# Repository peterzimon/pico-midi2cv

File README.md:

# MIDI to CV converter

## About
A simple MIDI to CV converter using MCP4288 DAC.

## Dependecies
Uses [`pico-lib`](https://github.com/peterzimon/pico-lib) submodule. Clone and pull 
with `--recurse-submodules`, or use `git submodule update --init` once cloned. 

Alternatively you can set `git config submodule.recurse true` or `git config --global submodule.recurse true`.

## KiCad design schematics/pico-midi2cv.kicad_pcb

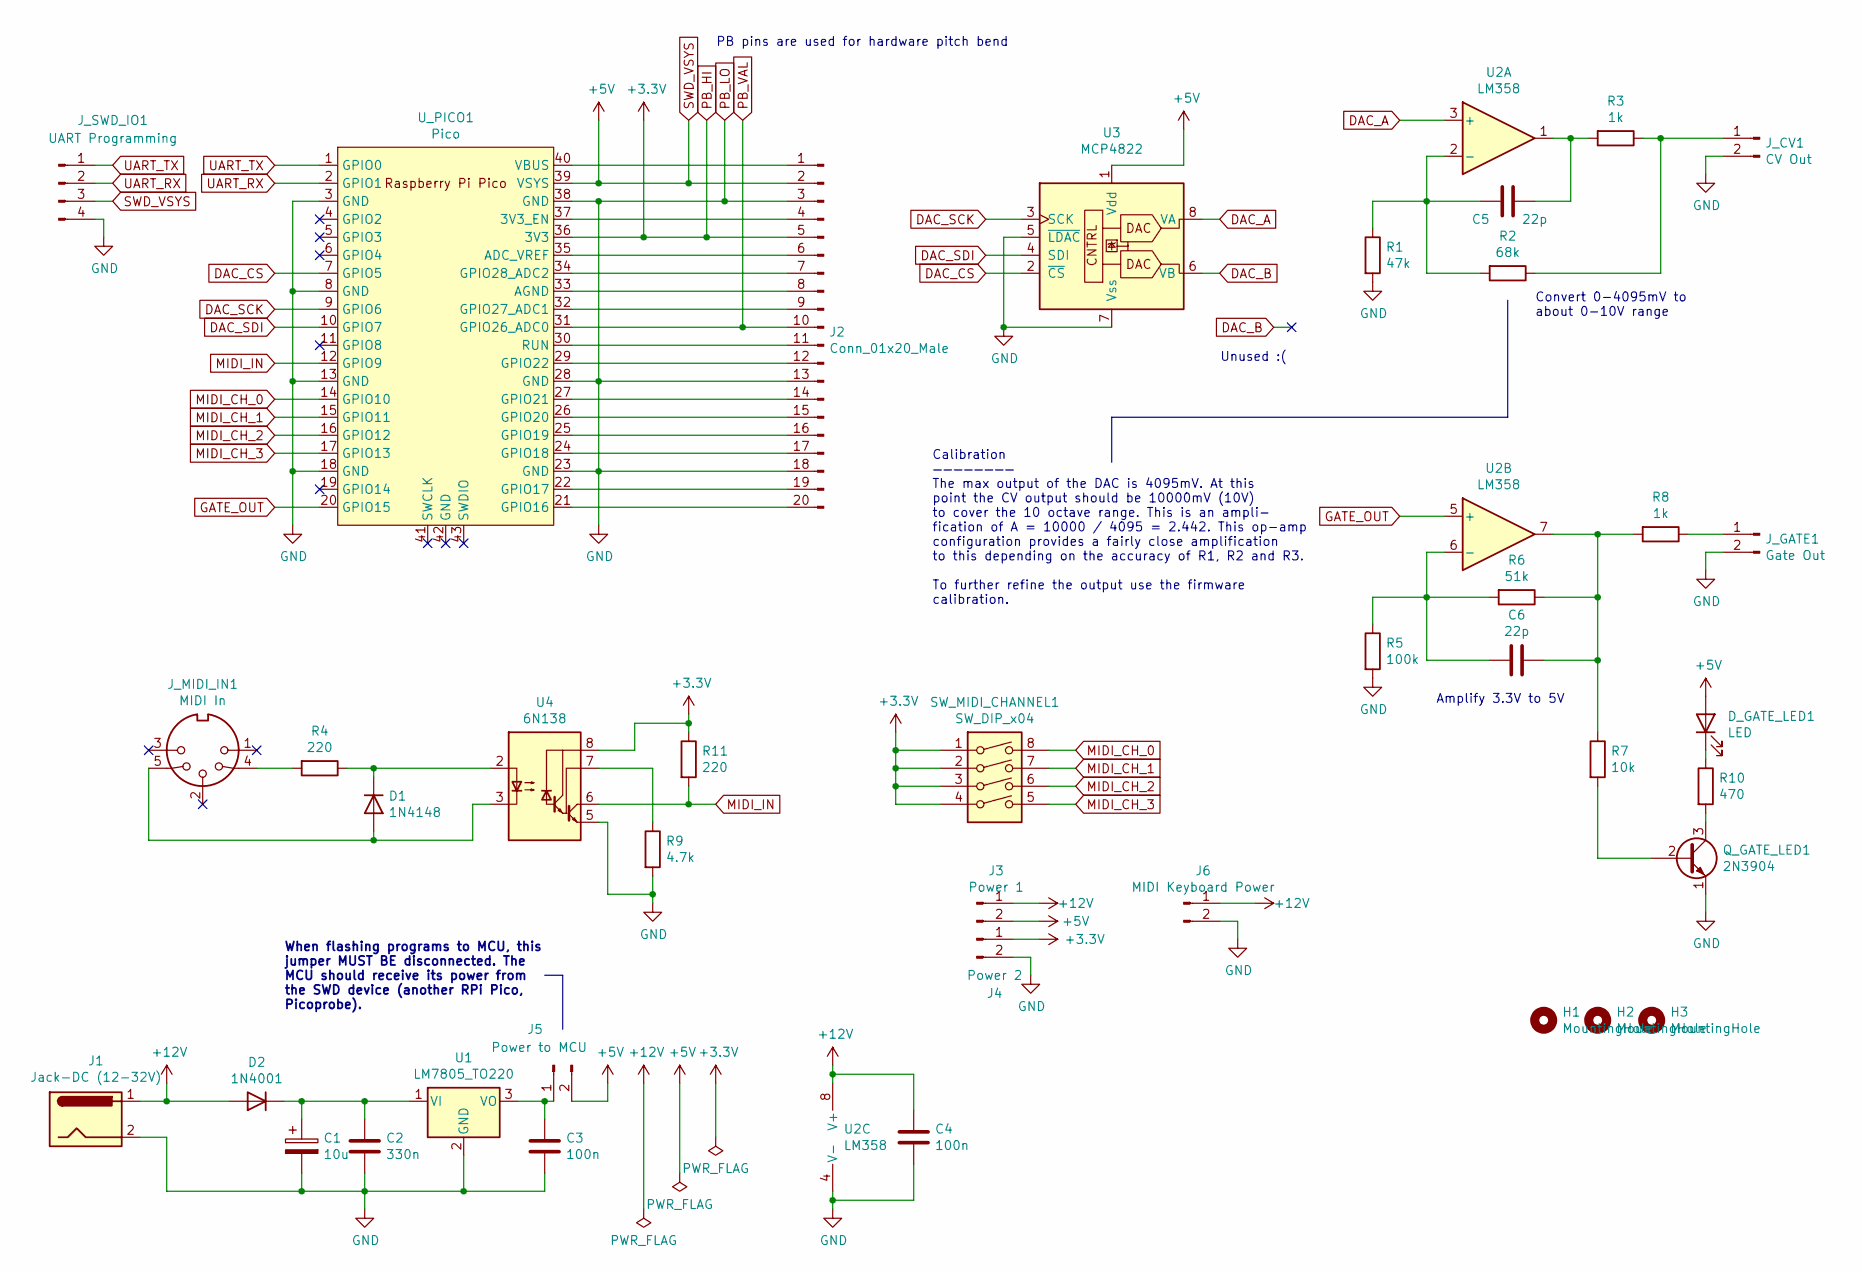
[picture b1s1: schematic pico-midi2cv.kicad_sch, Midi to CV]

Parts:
C1: 10u; CP_Radial_D5.0mm_P2.50mm
C2: 330n; C_Disc_D5.0mm_W2.5mm_P2.50mm
C3, C4: 100n; C_Disc_D5.0mm_W2.5mm_P2.50mm
C5, C6: 22p; C_Disc_D5.0mm_W2.5mm_P2.50mm
D1: 1N4148; D_Axial
D2: 1N4001; D_Axial
D_GATE_LED1: LED; NSL25_01x02_Vertical
H1, H2, H3: MountingHole; MountingHole_3mm
J1: Jack-DC (12-32V); NSL25_01x02_Vertical
J2: Conn_01x20_Male; PinOut_01x20
J3: Power 1; NSL25_01x02_Vertical
J4: Power 2; NSL25_01x02_Vertical
J5: Power to MCU; PinOut_01x02
J6: MIDI Keyboard Power; NSL25_01x02_Vertical
J_CV1: CV Out; NSL25_01x02_Vertical
J_GATE1: Gate Out; NSL25_01x02_Vertical
J_MIDI_IN1: MIDI In; PinOut_01x05
J_SWD_IO1: UART Programming; PinOut_01x04
Q_GATE_LED1: 2N3904; TO-92_Inline_Wide
R1: 47k; R_Axial_Vertical
R2: 68k; R_Axial_Vertical
R3, R8: 1k; R_Axial_Vertical
R4, R11: 220; R_Axial_Vertical
R5: 100k; R_Axial_Vertical
R6: 51k; R_Axial_Vertical
R7: 10k; R_Axial_Vertical
R9: 4.7k; R_Axial_Vertical
R10: 470; R_Axial_Vertical
SW_MIDI_CHANNEL1: SW_DIP_x04; SW_DIP_SPSTx04_Slide_6.7x11.72mm_W7.62mm_P2.54mm_LowProfile
U1: LM7805_TO220; TO-220-3_Vertical
U2: LM358; DIP-8_W7.62mm
U3: MCP4822; DIP-8_W7.62mm
U4: 6N138; DIP-8_W7.62mm
U_PICO1: Pico; RPi_Pico_SMD_TH

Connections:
+12V: C4.1, D2.2 (A), J1.1, J3.1, J6.1, U2.8 (V+)
DAC_A: U2.3 (+), U3.8 (VA)
DAC_B: U3.6 (VB)
DAC_CS: U3.2 (~CS), U_PICO1.7 (GPIO5)
DAC_SCK: U3.3 (SCK), U_PICO1.9 (GPIO6)
DAC_SDI: U3.4 (SDI), U_PICO1.10 (GPIO7)
GATE_OUT: U2.5 (+), U_PICO1.20 (GPIO15)
MIDI_CH_0: SW_MIDI_CHANNEL1.8, U_PICO1.14 (GPIO10)
MIDI_CH_1: SW_MIDI_CHANNEL1.7, U_PICO1.15 (GPIO11)
MIDI_CH_2: SW_MIDI_CHANNEL1.6, U_PICO1.16 (GPIO12)
MIDI_CH_3: SW_MIDI_CHANNEL1.5, U_PICO1.17 (GPIO13)
MIDI_IN: R11.2, U4.6 (VO2), U_PICO1.12 (GPIO9)
unnamed: C1.1, C2.1, D2.1 (K), U1.1 (VI)
unnamed: C3.1, J5.1, U1.3 (VO)
unnamed: C5.1, R3.2, U2.1
unnamed: C5.2, R1.1, R2.2, U2.2 (-)
unnamed: C6.1, R6.1, R7.1, R8.2, U2.7
unnamed: C6.2, R5.1, R6.2, U2.6 (-)
unnamed: D1.1 (K), R4.1, U4.2 (C1)
unnamed: D1.2 (A), J_MIDI_IN1.5, U4.3 (C2)
unnamed: D_GATE_LED1.1 (K), R10.1
unnamed: J2.1, U_PICO1.40 (VBUS)
unnamed: J2.4, U_PICO1.37 (3V3_EN)
unnamed: J2.6, U_PICO1.35 (ADC_VREF)
unnamed: J2.7, U_PICO1.34 (GPIO28_ADC2)
unnamed: J2.8, U_PICO1.33 (AGND)
unnamed: J2.9, U_PICO1.32 (GPIO27_ADC1)
unnamed: J2.11, U_PICO1.30 (RUN)
unnamed: J2.12, U_PICO1.29 (GPIO22)
unnamed: J2.14, U_PICO1.27 (GPIO21)
unnamed: J2.15, U_PICO1.26 (GPIO20)
unnamed: J2.16, U_PICO1.25 (GPIO19)
unnamed: J2.17, U_PICO1.24 (GPIO18)
unnamed: J2.19, U_PICO1.22 (GPIO17)
unnamed: J2.20, U_PICO1.21 (GPIO16)
unnamed: J_CV1.1, R2.1, R3.1
unnamed: J_GATE1.1, R8.1
unnamed: J_MIDI_IN1.4, R4.2
unnamed: Q_GATE_LED1.2 (B), R7.2
unnamed: Q_GATE_LED1.3 (C), R10.2
unnamed: R9.1, U4.7 (VO1)
PB_HI: J2.5, J4.1, R11.1, SW_MIDI_CHANNEL1.1, SW_MIDI_CHANNEL1.2, SW_MIDI_CHANNEL1.3, SW_MIDI_CHANNEL1.4, U4.8 (VCC), U_PICO1.36 (3V3)
PB_LO: C1.2, C2.2, C3.2, C4.2, J1.2, J2.3, J2.13, J2.18, J4.2, J6.2, J_CV1.2, J_GATE1.2, J_SWD_IO1.4, Q_GATE_LED1.1 (E), R1.2, R5.2, R9.2, U1.2 (GND), U2.4 (V-), U3.5 (~LDAC), U3.7 (Vss), U4.5 (GND), U_PICO1.3 (GND), U_PICO1.8 (GND), U_PICO1.13 (GND), U_PICO1.18 (GND), U_PICO1.23 (GND), U_PICO1.28 (GND), U_PICO1.38 (GND)
PB_VAL: J2.10, U_PICO1.31 (GPIO26_ADC0)
SWD_VSYS: D_GATE_LED1.2 (A), J2.2, J3.2, J5.2, J_SWD_IO1.3, U3.1 (Vdd), U_PICO1.39 (VSYS)
UART_RX: J_SWD_IO1.2, U_PICO1.2 (GPIO1)
UART_TX: J_SWD_IO1.1, U_PICO1.1 (GPIO0)

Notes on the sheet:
Amplify 3.3V to 5V
PB pins are used for hardware pitch bend
Convert 0-4095mV to about 0-10V range
Unused :(
When flashing programs to MCU, this jumper MUST BE disconnected. The MCU should receive its power from the SWD device (another RPi Pico, Picoprobe).
Calibration ———————— The max output of the DAC is 4095mV. At this point the CV output should be 10000mV (10V) to cover the 10 octave range. This is an ampli- fication of A = 10000 / 4095 = 2.442. This op-amp configuration provides a fairly close amplification to this depending on the accuracy of R1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

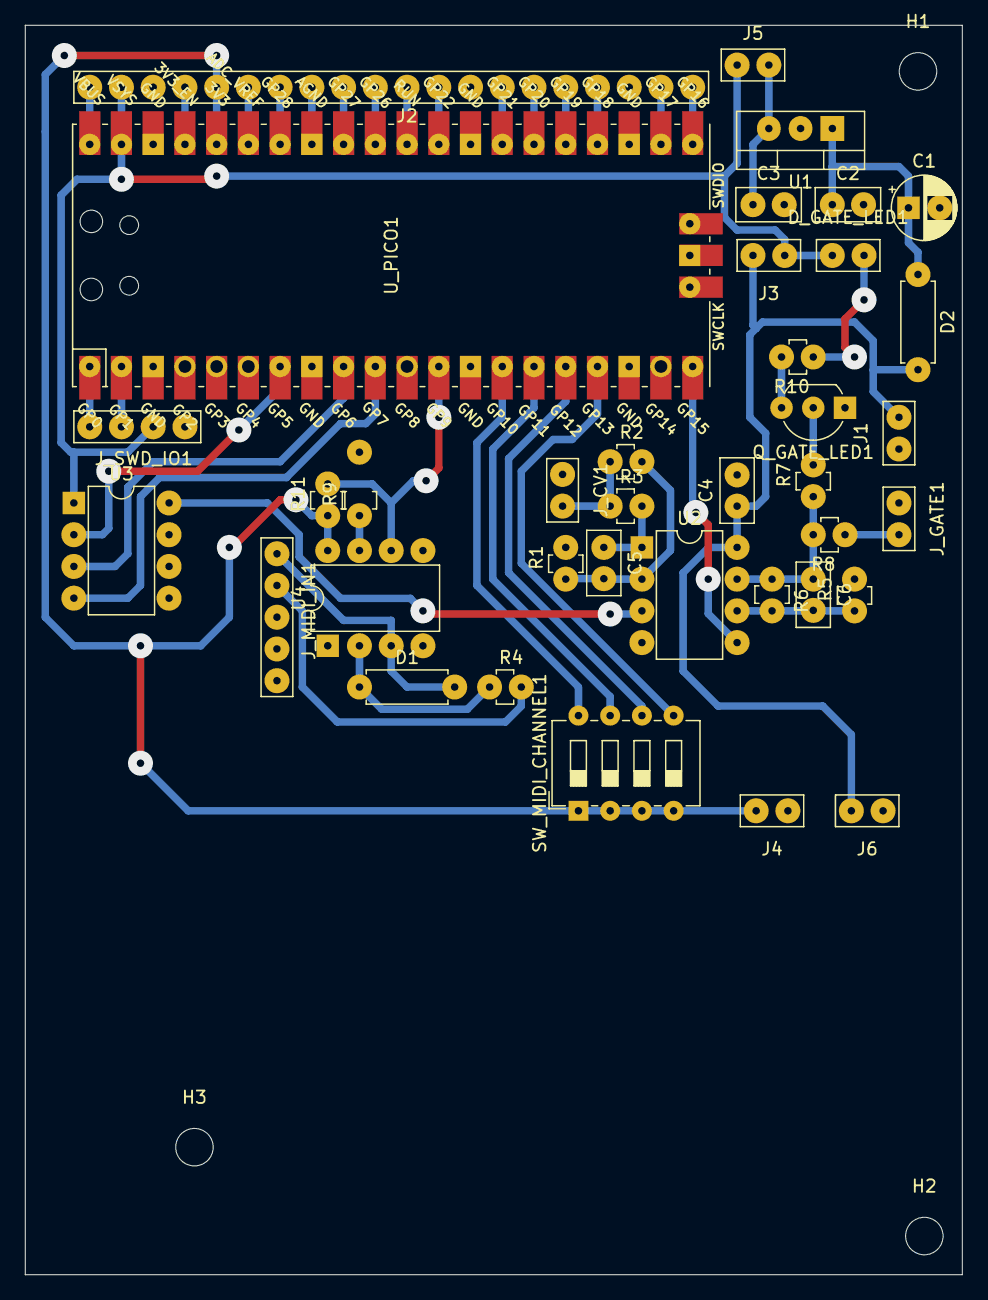
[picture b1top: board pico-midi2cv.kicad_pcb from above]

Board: 2 copper layers, 75.0 x 100.0 mm, 40 parts (0 on the bottom side), 46 nets.

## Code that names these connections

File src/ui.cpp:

#include "ui.h"

void UI::init() {
    // Read MIDI channel. Only do this once during bootup
    gpio_init(GP_CHANNEL_DIP_0); gpio_set_dir(GP_CHANNEL_DIP_0, GPIO_IN); gpio_pull_down(GP_CHANNEL_DIP_0);
    gpio_init(GP_CHANNEL_DIP_1); gpio_set_dir(GP_CHANNEL_DIP_1, GPIO_IN); gpio_pull_down(GP_CHANNEL_DIP_1);
    gpio_init(GP_CHANNEL_DIP_2); gpio_set_dir(GP_CHANNEL_DIP_2, GPIO_IN); gpio_pull_down(GP_CHANNEL_DIP_2);
    gpio_init(GP_CHANNEL_DIP_3); gpio_set_dir(GP_CHANNEL_DIP_3, GPIO_IN); gpio_pull_down(GP_CHANNEL_DIP_3);

    int midi_ch_0 = gpio_get(GP_CHANNEL_DIP_0);
    int midi_ch_1 = gpio_get(GP_CHANNEL_DIP_1);
    int midi_ch_2 = gpio_get(GP_CHANNEL_DIP_2);
    int midi_ch_3 = gpio_get(GP_CHANNEL_DIP_3);

    uint8_t midi_ch = midi_ch_0 | midi_ch_1 << 1 | midi_ch_2 << 2 | midi_ch_3;
    settings.midi_channel = midi_ch;

    printf("Midi channel: %d\r\n", midi_ch);

    // Pitchbend initialisation
    // Init ADC
    adc_init();
    adc_gpio_init(ADC_GP_PITCHBEND);

    // Select a GPIO port for input. 0 represents GPIO26, 1: GPIO27 etc. Subtract
    // 26 from the GPIO port number to get the mapping.
    adc_select_input(ADC_GP_PITCHBEND - 26);

    // Store initial value of pitchbend as a reference point
    m_pitchbend_reference = m_read_adc_samples(10);

    // printf("Pitchbend reference: %d", m_pitchbend_reference);
}

// Read all values on the UI
void UI::update() {
    m_update_pitchbend();
}

/**
 * Return the pitch bend value converted to MIDI value
 * 1. m_pitchbend_reference should be mapped to PITCH_BEND_CENTER (0x2000)
 * 2. m_pitchbend_reference +/- HW_PB_MAX_DIFF should be mapped to
 *    MAX_PITCH_BEND (0x3fff) and 0x0000 respectively
 * 3. Returned value should not be between 0 and 0x3fff
 */
uint16_t UI::hw_pb_to_midi_pb() {
    uint16_t midi_pitchbend = 0x0;
    uint16_t diff = 0;
    uint16_t ratio = 0;

    if (m_pitchbend > m_pitchbend_reference) {
        diff = m_pitchbend - m_pitchbend_reference;
        ratio = round(diff * 100 / HW_PB_MAX_DIFF);
        midi_pitchbend = uint16_t(PITCH_BEND_CENTER + (PITCH_BEND_CENTER * ratio / 100));
    } else if (m_pitchbend < m_pitchbend_reference) {
        diff = m_pitchbend_reference - m_pitchbend;
        ratio = round(diff * 100 / HW_PB_MAX_DIFF);
        midi_pitchbend = uint16_t(PITCH_BEND_CENTER - (PITCH_BEND_CENTER * ratio / 100));
    }

    return midi_pitchbend;
}

void UI::m_update_pitchbend() {
    adc_select_input(ADC_GP_PITCHBEND - 26);
    m_pitchbend = m_read_adc_samples(10);
}

uint16_t UI::m_read_adc_samples(size_t sample_size) {
    uint16_t value = 0;
    for (size_t i = 0; i < sample_size; i++) {
        value += adc_read();
    }
    return round(value / sample_size);
}

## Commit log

2022-01-30 Added pico-lib submodule
2022-01-30 Added Readme
2022-01-30 Udpated readme
2022-01-30 Updated submodule
2022-01-30 Updated CMakeLists to include pico-lib
2022-01-30 Updated submodules
2022-01-30 Added DAC support
2022-01-30 Added test DAC with library
2022-01-30 Updated lib
2022-01-30 Cleanup
2022-01-31 Added MIDI handler files
2022-02-01 Added base classes
2022-02-01 Updated namings
2022-02-01 Continue MIDI note handling
2022-02-01 Added single channel MIDI to CV converter
2022-02-02 Updated midi to cv logic + created schematics
2022-02-02 Fixed pitch bend + optimize performance
2022-06-03 Updated comments
2022-06-03 Updated schematics
2022-06-03 Uploaded schematics pdf's
2022-06-06 Added static MIDI channel setting
2022-06-06 Added MIDI channel DIP switch
2022-06-07 Added hardware joystick
2022-06-07 Added top 20 pin outs to PCB and further updates
2022-06-10 Bugfixes
2023-12-25 Updated to KiCad7 format
2023-12-26 Minor updates for standalone use
